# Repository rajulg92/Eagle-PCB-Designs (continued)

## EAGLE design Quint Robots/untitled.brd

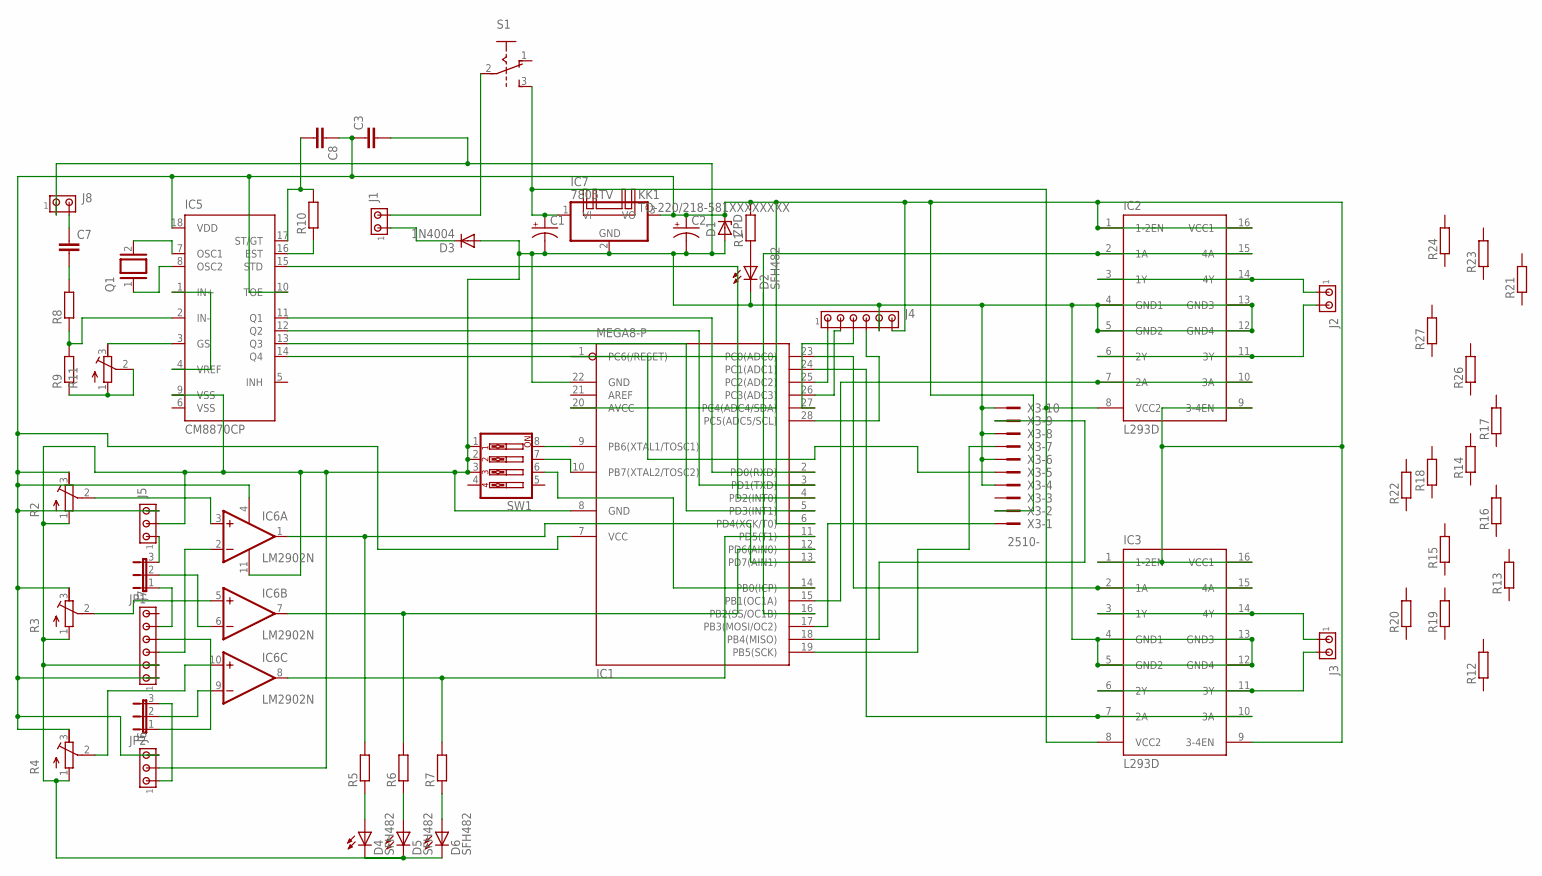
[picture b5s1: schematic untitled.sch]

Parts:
C1, C2: CPOL-USE5-10.5; E5-10,5
C3: C2.5/2; C2.5-2
C7, C8: C5/2.5; C5B2.5
D1: ZPD; DO35Z10
D2, D4, D5, D6: SFH482
D3: 1N4004; DO41-10
IC1: MEGA8-P; DIL28-3
IC2, IC3: L293D; DIL16
IC5: CM8870CP; DIL18
IC6: LM2902N; DIL14
IC7: 7805TV; TO220V
J1, J8: MTA02-100; 10X02MTA
J2, J3: MTA02-156; 1X2MTA
J4, J7: MTA06-100; 10X06MTA
J5, J6: MTA03-100; 10X03MTA
JP1, JP2: JP2E; JP2
KK1: TO-220/218-581XXXXXXXX; 581XXXXXXXX
Q1: XTAL/S; QS
R1, R5, R6, R7, R8, R9, R10, R12: R-EU_0207/10; 0207/10
R2, R3, R4, R11: R-TRIMM3296W; RTRIM3296W
R13, R14, R15, R16, R17, R18, R19, R20, R22, R26, R27: R-EU_0204/7; 0204/7
R21, R23, R24: R-EU_0207/12; 0207/12
S1: A68-A31
SW1: SW_DIP-4; EDG-04
X3: 2510-; PAK100/2500-10

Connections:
unnamed: IC1.16 (PB2(SS/OC1B)), IC2.2 (1A), IC2.15 (4A)
unnamed: IC2.3 (1Y), IC2.14 (4Y), J2.1
unnamed: IC1.9 (PB6(XTAL1/TOSC1)), SW1.8
unnamed: IC1.13 (PD7(AIN1)), IC6.1 (OUT), R5.2
unnamed: IC2.6 (2Y), IC2.11 (3Y), J2.2
unnamed: IC1.15 (PB1(OC1A)), IC2.7 (2A), IC2.10 (3A)
unnamed: IC1.23 (PC0(ADC0)), IC3.2 (1A), IC3.15 (4A)
unnamed: IC3.3 (1Y), IC3.14 (4Y), J3.1
unnamed: IC1.17 (PB3(MOSI/OC2)), X3.1
unnamed: D2.A, R1.1
unnamed: IC3.6 (2Y), IC3.11 (3Y), J3.2
unnamed: IC1.24 (PC1(ADC1)), IC3.7 (2A), IC3.10 (3A)
unnamed: IC1.1 (PC6(/RESET)), X3.5
unnamed: IC1.19 (PB5(SCK)), X3.7
unnamed: D4.A, R5.1
unnamed: IC1.18 (PB4(MISO)), X3.9
unnamed: IC1.25 (PC2(ADC2)), J4.6 (1)
unnamed: IC1.26 (PC3(ADC3)), J4.5 (2)
unnamed: IC1.27 (PC4(ADC4/SDA)), J4.4 (3)
unnamed: IC1.28 (PC5(ADC5/SCL)), J4.3 (4)
unnamed: C1.+, IC2.8 (VCC2), IC3.8 (VCC2), IC7.1 (VI), S1.3 (S)
unnamed: IC1.10 (PB7(XTAL2/TOSC2)), SW1.7
unnamed: IC1.14 (PB0(ICP)), SW1.6
unnamed: J5.1, JP1.3
unnamed: IC6.2 (-IN), J7.4 (3)
unnamed: IC6.6 (-IN), JP1.2
unnamed: IC6.9 (-IN), JP2.2
unnamed: IC6.3 (+IN), R2.2 (S)
unnamed: IC6.5 (+IN), R3.2 (S)
unnamed: IC6.10 (+IN), R4.2 (S)
unnamed: IC1.5 (PD3(INT1)), IC5.13 (Q3)
unnamed: IC5.7 (OSC1), Q1.2
unnamed: D5.A, R6.1
unnamed: D6.A, R7.1
unnamed: C1.-, C2.-, C3.2, D1.A, D2.K (C), D3.A, D4.K (C), D5.K (C), D6.K (C), IC1.8 (GND), IC1.22 (GND), IC2.4 (GND1), IC2.5 (GND2), IC2.12 (GND4), IC2.13 (GND3), IC3.4 (GND1), IC3.5 (GND2), IC3.12 (GND4), IC3.13 (GND3), IC5.9 (VSS), IC6.11 (V-), IC7.2 (GND), J4.2 (5), J5.2, J6.2, J7.5 (2), J8.1, R2.1 (E), R3.1 (E), R4.1 (E), SW1.1, SW1.2, SW1.3, X3.4, X3.6, X3.8, X3.10
unnamed: IC1.12 (PD6(AIN0)), IC6.7 (OUT), R6.2
unnamed: IC1.11 (PD5(T1)), IC6.8 (OUT), R7.2
unnamed: IC5.8 (OSC2), Q1.1
unnamed: J7.3 (4), JP2.1
unnamed: J7.2 (5), JP1.1
unnamed: J1.2, S1.2
unnamed: J6.1, JP2.3
unnamed: IC5.1 (IN+), IC5.4 (VREF)
unnamed: IC1.2 (PD0(RXD)), IC5.11 (Q1)
unnamed: IC1.3 (PD1(TXD)), IC5.12 (Q2)
unnamed: IC1.6 (PD4(XCK/T0)), IC5.14 (Q4)
unnamed: IC1.4 (PD2(INT0)), IC5.15 (STD)
unnamed: R9.1, R11.1 (E), R11.2 (S)
unnamed: C7.1, J8.2
unnamed: C7.2, R8.2
unnamed: IC5.2 (IN-), R8.1, R9.2
unnamed: C2.+, C3.1, C8.1, D1.C, IC1.7 (VCC), IC1.20 (AVCC), IC2.1 (1-2EN), IC2.9 (3-4EN), IC2.16 (VCC1), IC3.1 (1-2EN), IC3.9 (3-4EN), IC3.16 (VCC1), IC5.10 (TOE), IC5.18 (VDD), IC6.4 (V+), IC7.3 (VO), J4.1 (6), J5.3, J6.3, J7.6 (1), R1.2, R2.3 (A), R3.3 (A), R4.3 (A), X3.2
unnamed: IC5.3 (GS), R11.3 (A)
unnamed: C8.2, IC5.17 (ST/GT), R10.2
unnamed: IC5.16 (EST), R10.1
unnamed: D3.C, J1.1
VSS: IC5.6 (VSS)

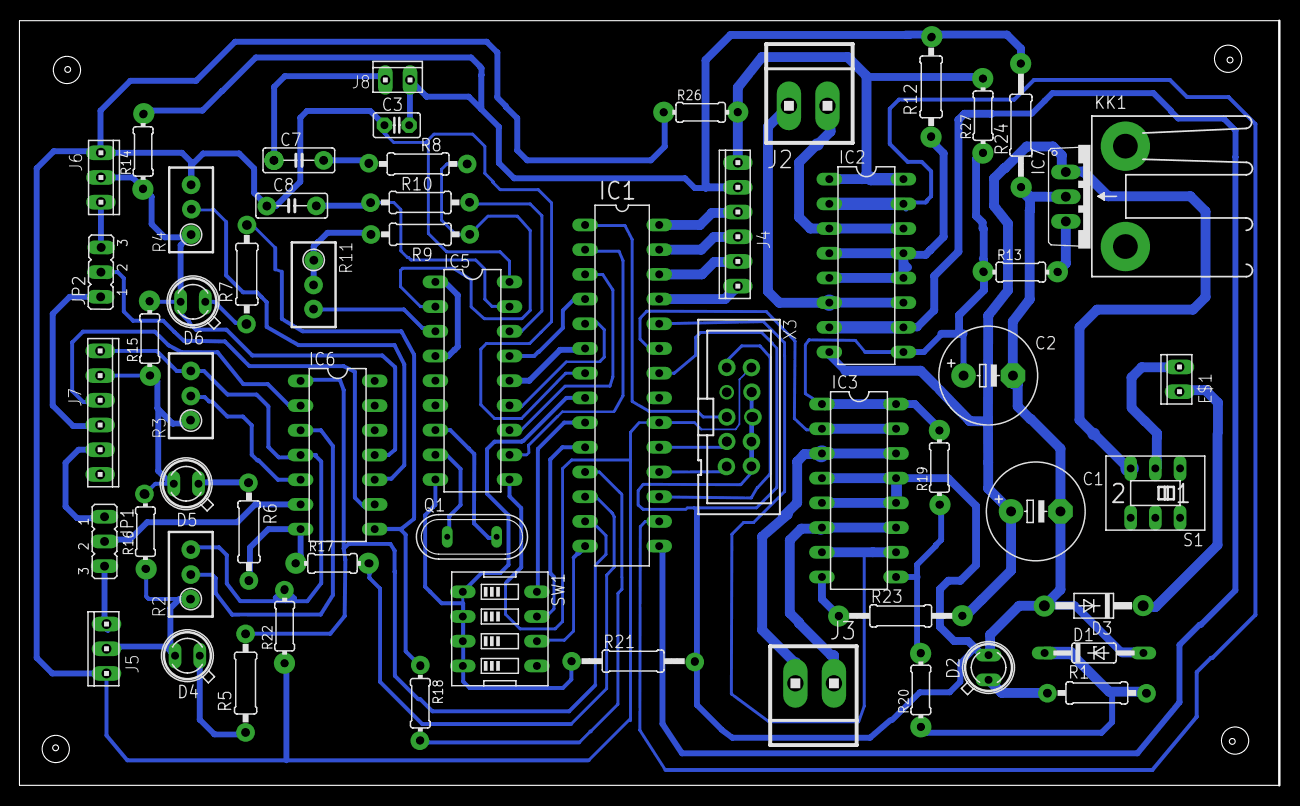
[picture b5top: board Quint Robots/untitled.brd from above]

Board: 2 copper layers, 129.5 x 78.6 mm, 58 parts (0 on the bottom side), 54 nets.

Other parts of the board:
E$1: 10X02MTA
